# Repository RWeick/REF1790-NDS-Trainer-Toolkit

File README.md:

# REF1790-NDS-Trainer-Toolkit
The full schematic and gerbers for the Nintendo DS Trainer Toolkit by Datel. The original PCB has a bodged 1k Ohm resistor on it. The traces have been corrected so that it is no longer necessary, and a SMD resistor is used instead.

PCB Thickness: 0.8 mm

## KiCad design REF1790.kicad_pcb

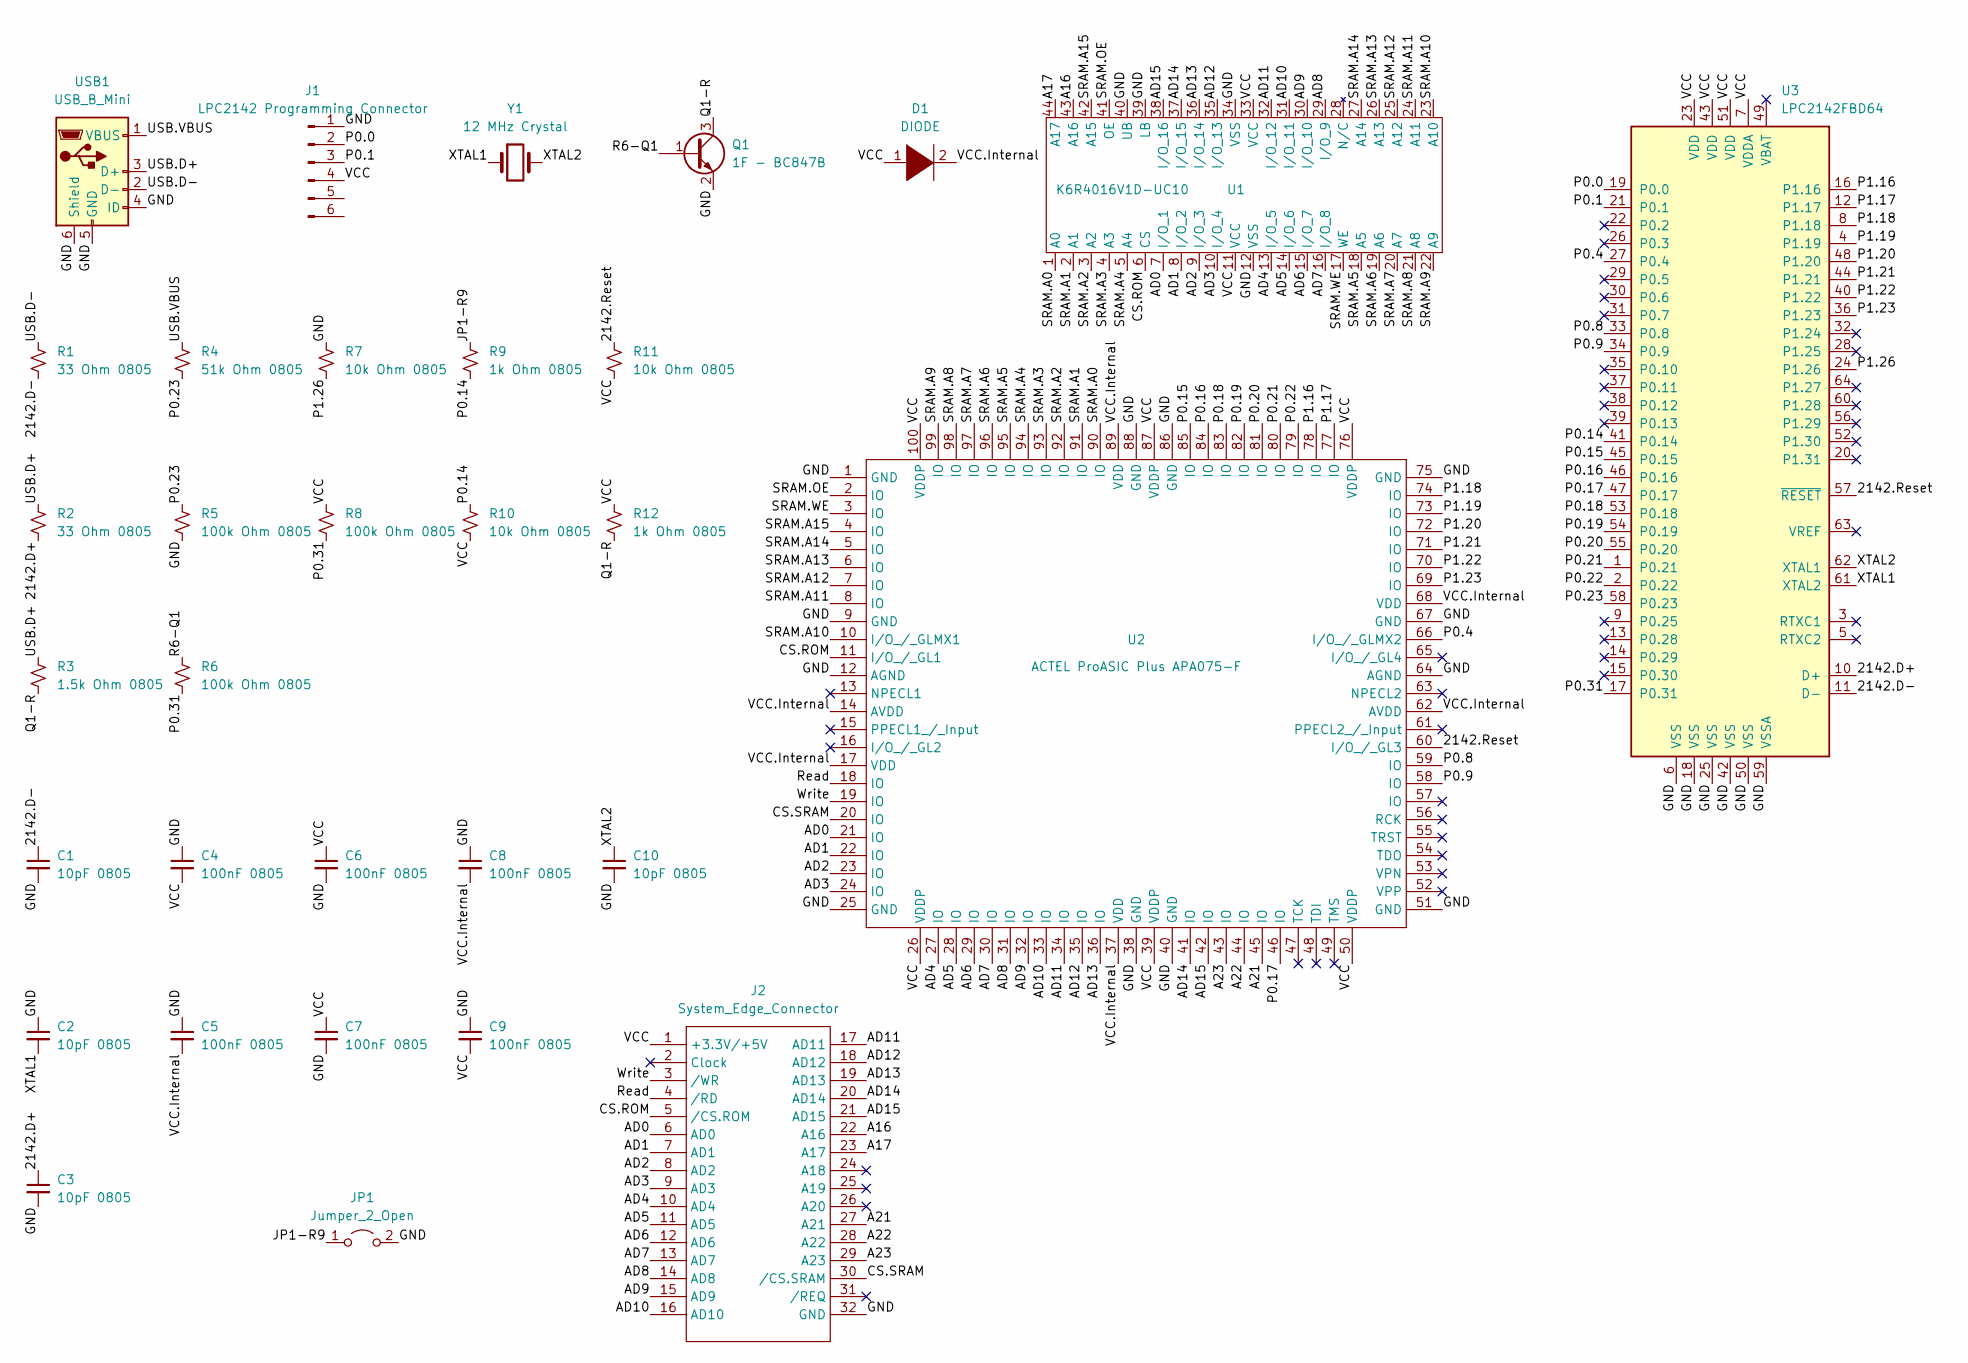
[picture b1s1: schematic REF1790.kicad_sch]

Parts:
C1, C2, C3, C10: 10pF 0805; SMD Cap and Res
C4, C5, C6, C7, C8, C9: 100nF 0805; SMD Cap and Res
D1: DIODE; Diode
J1: LPC2142 Programming Connector; LPC Programming Port
J2: System_Edge_Connector; Edge Connector
JP1: Jumper_2_Open; Jumper Pads
Q1: 1F - BC847B; Transistor
R1, R2: 33 Ohm 0805; SMD Cap and Res
R3: 1.5k Ohm 0805; SMD Cap and Res
R4: 51k Ohm 0805; SMD Cap and Res
R5, R6, R8: 100k Ohm 0805; SMD Cap and Res
R7, R10, R11: 10k Ohm 0805; SMD Cap and Res
R9, R12: 1k Ohm 0805; SMD Cap and Res
U1: K6R4016V1D-UC10
U2: ACTEL ProASIC Plus APA075-F; GBA AR Max FPGA
U3: LPC2142FBD64; LPC2142
USB1: USB_B_Mini; USB_Mini_B
Y1: 12 MHz Crystal; Crystal Clock

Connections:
/2142.D+: C3.1, R2.2, U3.10 (D+)
/2142.D-: C1.1, R1.2, U3.11 (D-)
/2142.Reset: R11.1, U2.60 (I/O_/_GL3), U3.57 (~RESET)
/A16: J2.22 (A16), U1.43 (A16)
/A17: J2.23 (A17), U1.44 (A17)
/A21: J2.27 (A21), U2.45 (IO)
/A22: J2.28 (A22), U2.44 (IO)
/A23: J2.29 (A23), U2.43 (IO)
/AD0: J2.6 (AD0), U1.7 (I/O_1), U2.21 (IO)
/AD1: J2.7 (AD1), U1.8 (I/O_2), U2.22 (IO)
/AD2: J2.8 (AD2), U1.9 (I/O_3), U2.23 (IO)
/AD3: J2.9 (AD3), U1.10 (I/O_4), U2.24 (IO)
/AD4: J2.10 (AD4), U1.13 (I/O_5), U2.27 (IO)
/AD5: J2.11 (AD5), U1.14 (I/O_6), U2.28 (IO)
/AD6: J2.12 (AD6), U1.15 (I/O_7), U2.29 (IO)
/AD7: J2.13 (AD7), U1.16 (I/O_8), U2.30 (IO)
/AD8: J2.14 (AD8), U1.29 (I/O_9), U2.31 (IO)
/AD9: J2.15 (AD9), U1.30 (I/O_10), U2.32 (IO)
/AD10: J2.16 (AD10), U1.31 (I/O_11), U2.33 (IO)
/AD11: J2.17 (AD11), U1.32 (I/O_12), U2.34 (IO)
/AD12: J2.18 (AD12), U1.35 (I/O_13), U2.35 (IO)
/AD13: J2.19 (AD13), U1.36 (I/O_14), U2.36 (IO)
/AD14: J2.20 (AD14), U1.37 (I/O_15), U2.41 (IO)
/AD15: J2.21 (AD15), U1.38 (I/O_16), U2.42 (IO)
/CS.ROM: J2.5 (/CS.ROM), U1.6 (CS), U2.11 (I/O_/_GL1)
/CS.SRAM: J2.30 (/CS.SRAM), U2.20 (IO)
/GND: C1.2, C2.1, C3.2, C4.1, C5.1, C6.2, C7.2, C8.1, C9.1, C10.2, J1.1, J2.32 (GND), JP1.2 (B), Q1.2 (E), R5.2, R7.1, U1.12 (VSS), U1.34 (VSS), U1.39 (LB), U1.40 (UB), U2.1 (GND), U2.9 (GND), U2.12 (AGND), U2.25 (GND), U2.38 (GND), U2.40 (GND), U2.51 (GND), U2.64 (AGND), U2.67 (GND), U2.75 (GND), U2.86 (GND), U2.88 (GND), U3.6 (VSS), U3.18 (VSS), U3.25 (VSS), U3.42 (VSS), U3.50 (VSS), U3.59 (VSSA), USB1.4 (ID), USB1.5 (GND), USB1.6 (Shield)
/JP1-R9: JP1.1 (A), R9.1
/P0.0: J1.2, U3.19 (P0.0)
/P0.1: J1.3, U3.21 (P0.1)
/P0.4: U2.66 (I/O_/_GLMX2), U3.27 (P0.4)
/P0.8: U2.59 (IO), U3.33 (P0.8)
/P0.9: U2.58 (IO), U3.34 (P0.9)
/P0.14: R9.2, R10.1, U3.41 (P0.14)
/P0.15: U2.85 (IO), U3.45 (P0.15)
/P0.16: U2.84 (IO), U3.46 (P0.16)
/P0.17: U2.46 (IO), U3.47 (P0.17)
/P0.18: U2.83 (IO), U3.53 (P0.18)
/P0.19: U2.82 (IO), U3.54 (P0.19)
/P0.20: U2.81 (IO), U3.55 (P0.20)
/P0.21: U2.80 (IO), U3.1 (P0.21)
/P0.22: U2.79 (IO), U3.2 (P0.22)
/P0.23: R4.2, R5.1, U3.58 (P0.23)
/P0.31: R6.2, R8.2, U3.17 (P0.31)
/P1.16: U2.78 (IO), U3.16 (P1.16)
/P1.17: U2.77 (IO), U3.12 (P1.17)
/P1.18: U2.74 (IO), U3.8 (P1.18)
/P1.19: U2.73 (IO), U3.4 (P1.19)
/P1.20: U2.72 (IO), U3.48 (P1.20)
/P1.21: U2.71 (IO), U3.44 (P1.21)
/P1.22: U2.70 (IO), U3.40 (P1.22)
/P1.23: U2.69 (IO), U3.36 (P1.23)
/P1.26: R7.2, U3.24 (P1.26)
/Q1-R: Q1.3 (C), R3.2, R12.2
/R6-Q1: Q1.1 (B), R6.1
/Read: J2.4 (/RD), U2.18 (IO)
/SRAM.A0: U1.1 (A0), U2.90 (IO)
/SRAM.A1: U1.2 (A1), U2.91 (IO)
/SRAM.A2: U1.3 (A2), U2.92 (IO)
/SRAM.A3: U1.4 (A3), U2.93 (IO)
/SRAM.A4: U1.5 (A4), U2.94 (IO)
/SRAM.A5: U1.18 (A5), U2.95 (IO)
/SRAM.A6: U1.19 (A6), U2.96 (IO)
/SRAM.A7: U1.20 (A7), U2.97 (IO)
/SRAM.A8: U1.21 (A8), U2.98 (IO)
/SRAM.A9: U1.22 (A9), U2.99 (IO)
/SRAM.A10: U1.23 (A10), U2.10 (I/O_/_GLMX1)
/SRAM.A11: U1.24 (A11), U2.8 (IO)
/SRAM.A12: U1.25 (A12), U2.7 (IO)
/SRAM.A13: U1.26 (A13), U2.6 (IO)
/SRAM.A14: U1.27 (A14), U2.5 (IO)
/SRAM.A15: U1.42 (A15), U2.4 (IO)
/SRAM.OE: U1.41 (OE), U2.2 (IO)
/SRAM.WE: U1.17 (WE), U2.3 (IO)
/USB.D+: R2.1, R3.1, USB1.3 (D+)
/USB.D-: R1.1, USB1.2 (D-)
/USB.VBUS: R4.1, USB1.1 (VBUS)
/VCC: C4.2, C6.1, C7.1, C9.2, D1.1 (K), J1.4, J2.1 (+3.3V/+5V), R8.1, R10.2, R11.2, R12.1, U1.11 (VCC), U1.33 (VCC), U2.26 (VDDP), U2.39 (VDDP), U2.50 (VDDP), U2.76 (VDDP), U2.87 (VDDP), U2.100 (VDDP), U3.7 (VDDA), U3.23 (VDD), U3.43 (VDD), U3.51 (VDD)
/VCC.Internal: C5.2, C8.2, D1.2 (A), U2.14 (AVDD), U2.17 (VDD), U2.37 (VDD), U2.62 (AVDD), U2.68 (VDD), U2.89 (VDD)
/Write: J2.3 (/WR), U2.19 (IO)
/XTAL1: C2.2, U3.61 (XTAL2), Y1.1
/XTAL2: C10.1, U3.62 (XTAL1), Y1.2

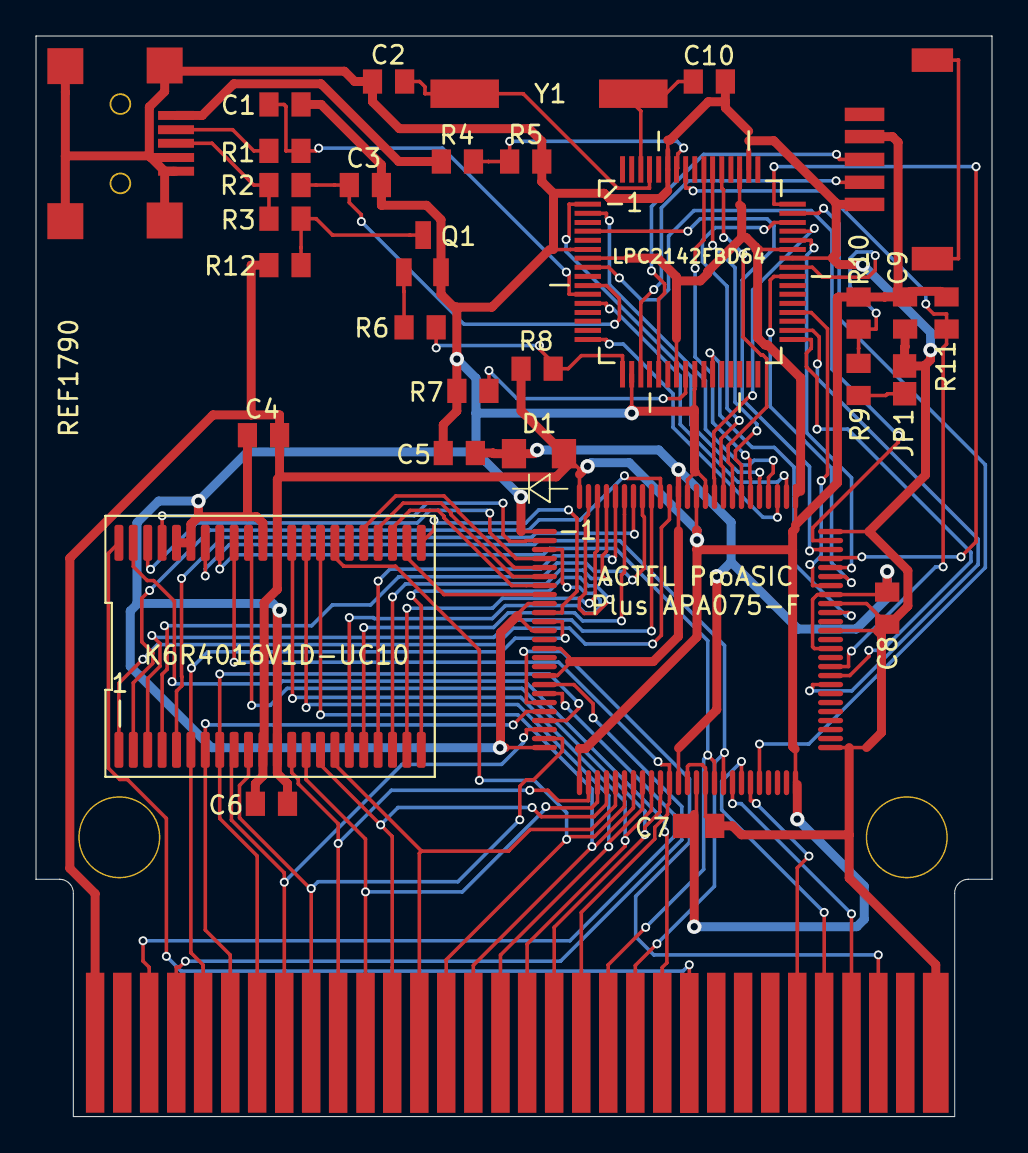
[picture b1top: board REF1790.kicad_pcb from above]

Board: 2 copper layers, 53.1 x 60.0 mm, 35 parts (0 on the bottom side), 82 nets.

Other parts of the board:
DiodeIndicator: 867ee1a9-3078-458d-9784-2b6d66f4ccf8
Hole, Hole1: Through Hole
